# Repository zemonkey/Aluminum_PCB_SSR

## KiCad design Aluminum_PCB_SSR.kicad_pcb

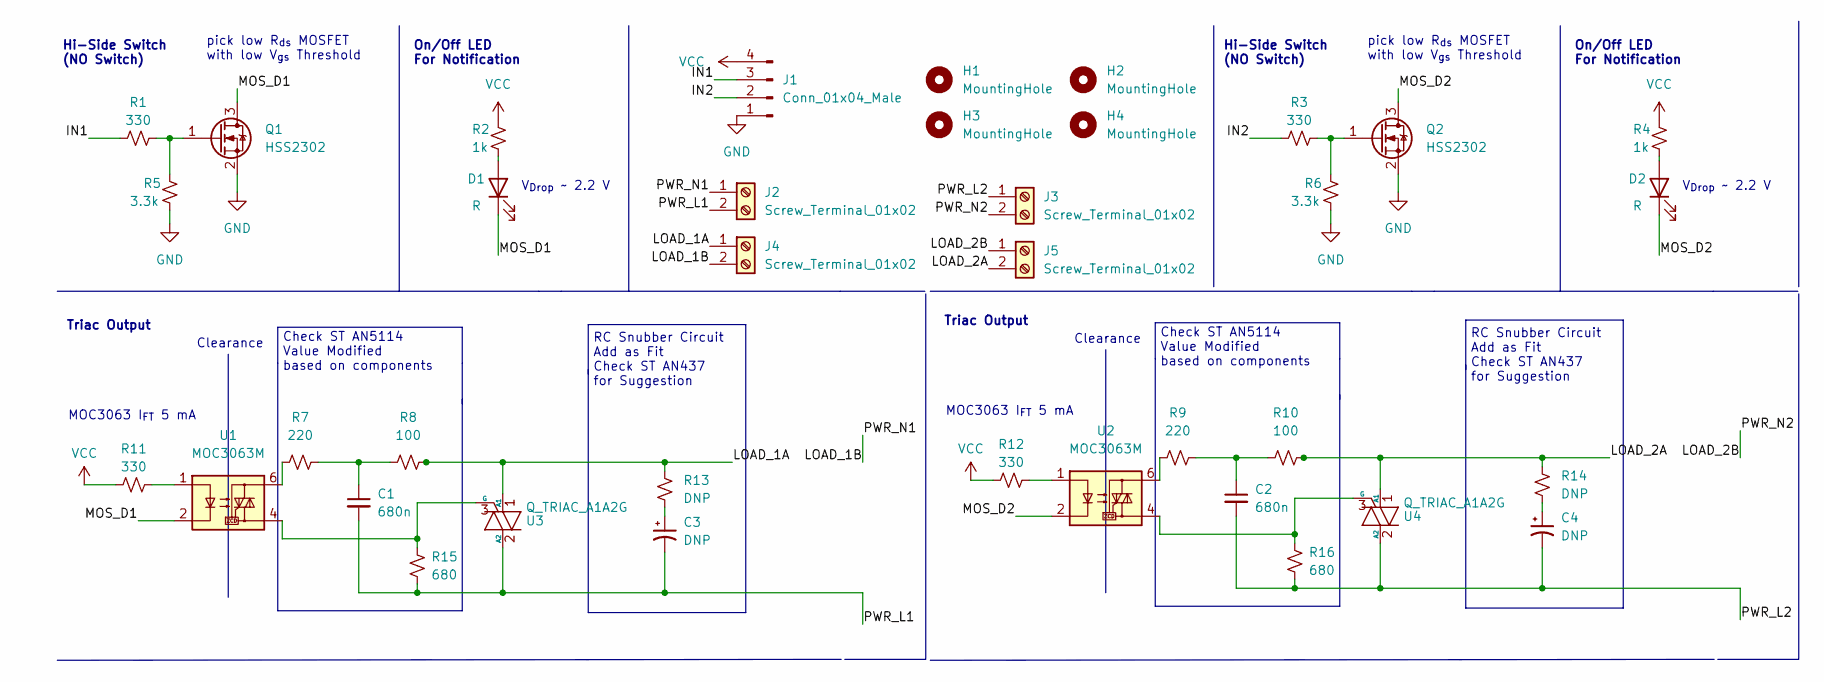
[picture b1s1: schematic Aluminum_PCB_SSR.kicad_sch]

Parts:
C1, C2: 680n; C_Rect_L11.5mm_W7.5mm_P10.00mm_MKT
C3, C4: DNP; C_Rect_L11.5mm_W7.5mm_P10.00mm_MKT
D1, D2: R; LED_0805_2012Metric_Pad1.15x1.40mm_HandSolder
H1, H2, H3, H4: MountingHole; MountingHole_3.2mm_M3_DIN965
J1: Conn_01x04_Male; PinHeader_1x04_P2.54mm_Vertical
J2, J3, J4, J5: Screw_Terminal_01x02; TerminalBlock_RND_205-00012_1x02_P5.00mm_Horizontal
Q1, Q2: HSS2302; SOT-23_Handsoldering
R1, R3, R11, R12: 330; R_0805_2012Metric_Pad1.20x1.40mm_HandSolder
R2, R4: 1k; R_0805_2012Metric_Pad1.20x1.40mm_HandSolder
R5, R6: 3.3k; R_0805_2012Metric_Pad1.20x1.40mm_HandSolder
R7, R9: 220; R_Axial_DIN0614_L14.3mm_D5.7mm_P20.32mm_Horizontal
R8, R10: 100; R_Axial_DIN0614_L14.3mm_D5.7mm_P20.32mm_Horizontal
R13, R14: DNP; R_Axial_DIN0614_L14.3mm_D5.7mm_P20.32mm_Horizontal
R15, R16: 680; R_Axial_DIN0614_L14.3mm_D5.7mm_P20.32mm_Horizontal
U1, U2: MOC3063M; DIP-6_W7.62mm
U3, U4: Q_TRIAC_A1A2G; TO-252-2

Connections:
/IN1: J1.3, R1.2
/IN2: J1.2, R3.2
/LOAD_1A: J4.1, R8.2, R13.1, U3.1 (A1)
/LOAD_1B: J2.1, J4.2
/LOAD_2A: J5.2, R10.2, R14.1, U4.1 (A1)
/LOAD_2B: J3.2, J5.1
/MOS_D1: D1.1 (K), Q1.3 (D), U1.2
/MOS_D2: D2.1 (K), Q2.3 (D), U2.2
/PWR_L1: C1.2, C3.2, J2.2, R15.2, U3.2 (A2)
/PWR_L2: C2.2, C4.2, J3.1, R16.2, U4.2 (A2)
GND: J1.1, Q1.2 (S), Q2.2 (S), R5.2, R6.2
unnamed: C1.1, R7.2, R8.1
unnamed: C2.1, R9.2, R10.1
unnamed: C3.1, R13.2
unnamed: C4.1, R14.2
unnamed: D1.2 (A), R2.2
unnamed: D2.2 (A), R4.2
unnamed: Q1.1 (G), R1.1, R5.1
unnamed: Q2.1 (G), R3.1, R6.1
unnamed: R7.1, U1.6
unnamed: R9.1, U2.6
unnamed: R11.1, U1.1
unnamed: R12.1, U2.1
unnamed: R15.1, U1.4, U3.3 (G)
unnamed: R16.1, U2.4, U4.3 (G)
VCC: J1.4, R2.1, R4.1, R11.2, R12.2

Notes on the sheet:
MOC3063 I_{FT} 5 mA
On/Off LED For Notification
Hi-Side Switch (NO Switch)
Check ST AN5114 Value Modified based on components
Clearance
pick low R_{ds} MOSFET with low V_{gs} Threshold
RC Snubber Circuit Add as Fit Check ST AN437 for Suggestion
V_{Drop} ~ 2.2 V
Triac Output

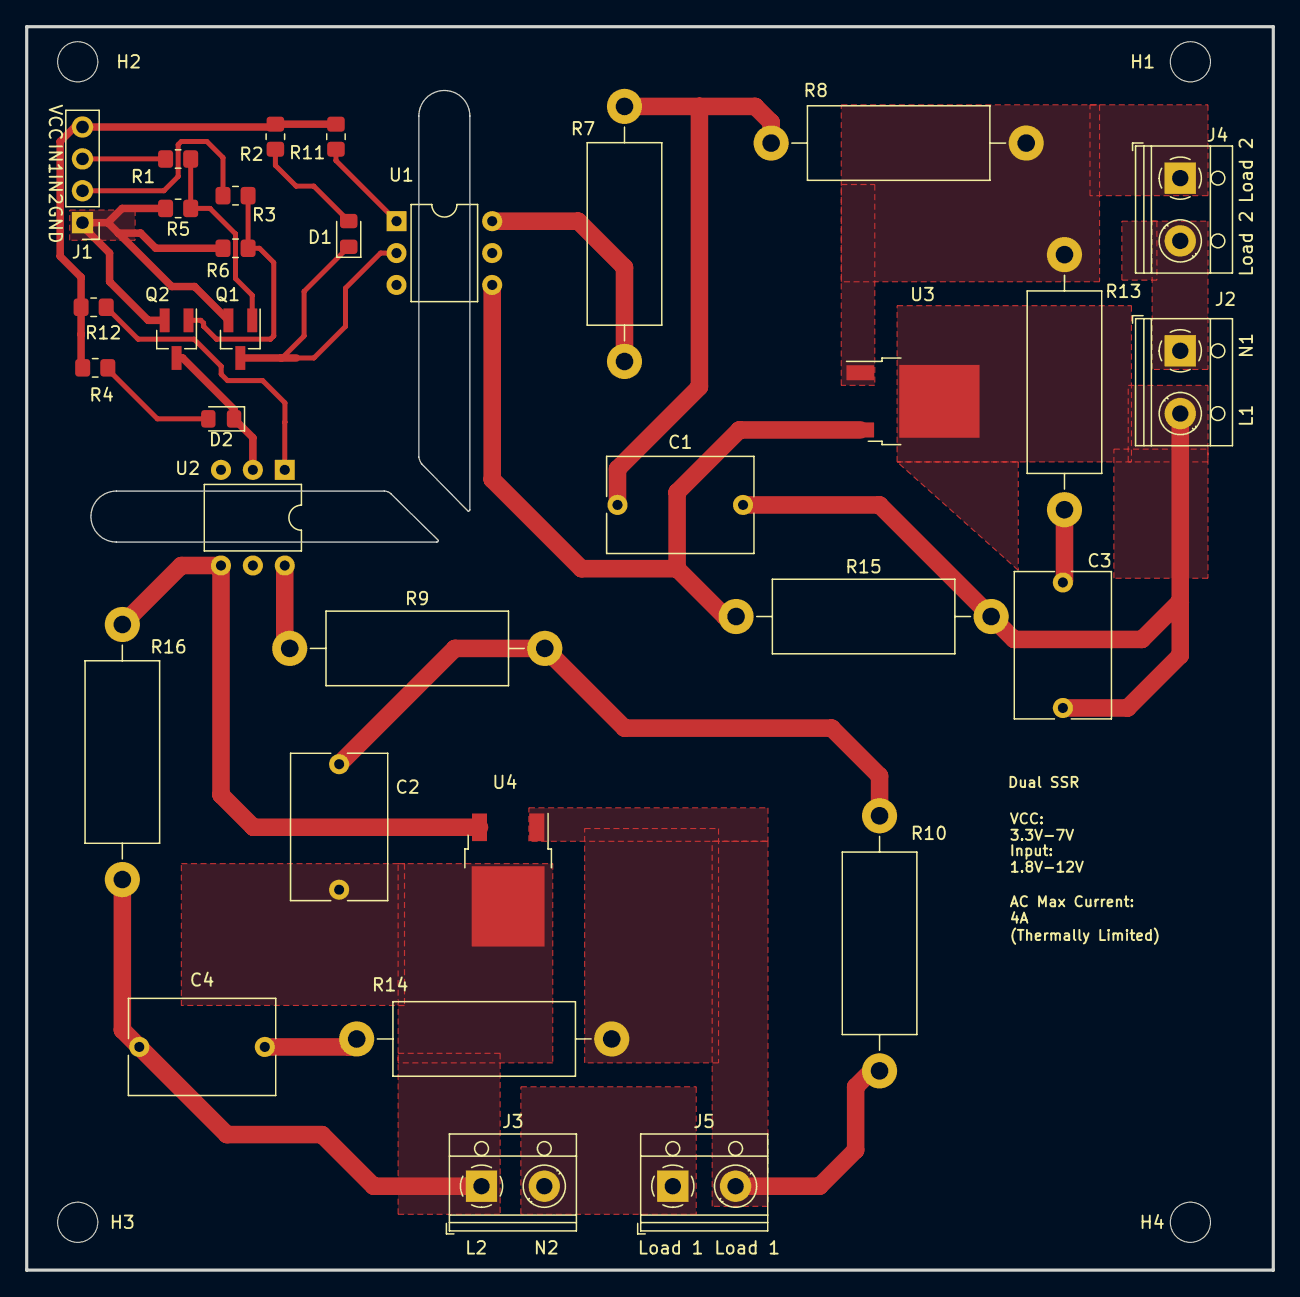
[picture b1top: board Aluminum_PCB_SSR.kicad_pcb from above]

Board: 4 copper layers, 99.3 x 99.1 mm, 37 parts (0 on the bottom side), 26 nets.
